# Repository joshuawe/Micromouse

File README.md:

# Micromouse
Micromouse TUM (Wintersemesester 2021/2022)

This is the repository of the Micromouse team of:
+ Marius
+ Michelle
+ Miriam
+ Joshua

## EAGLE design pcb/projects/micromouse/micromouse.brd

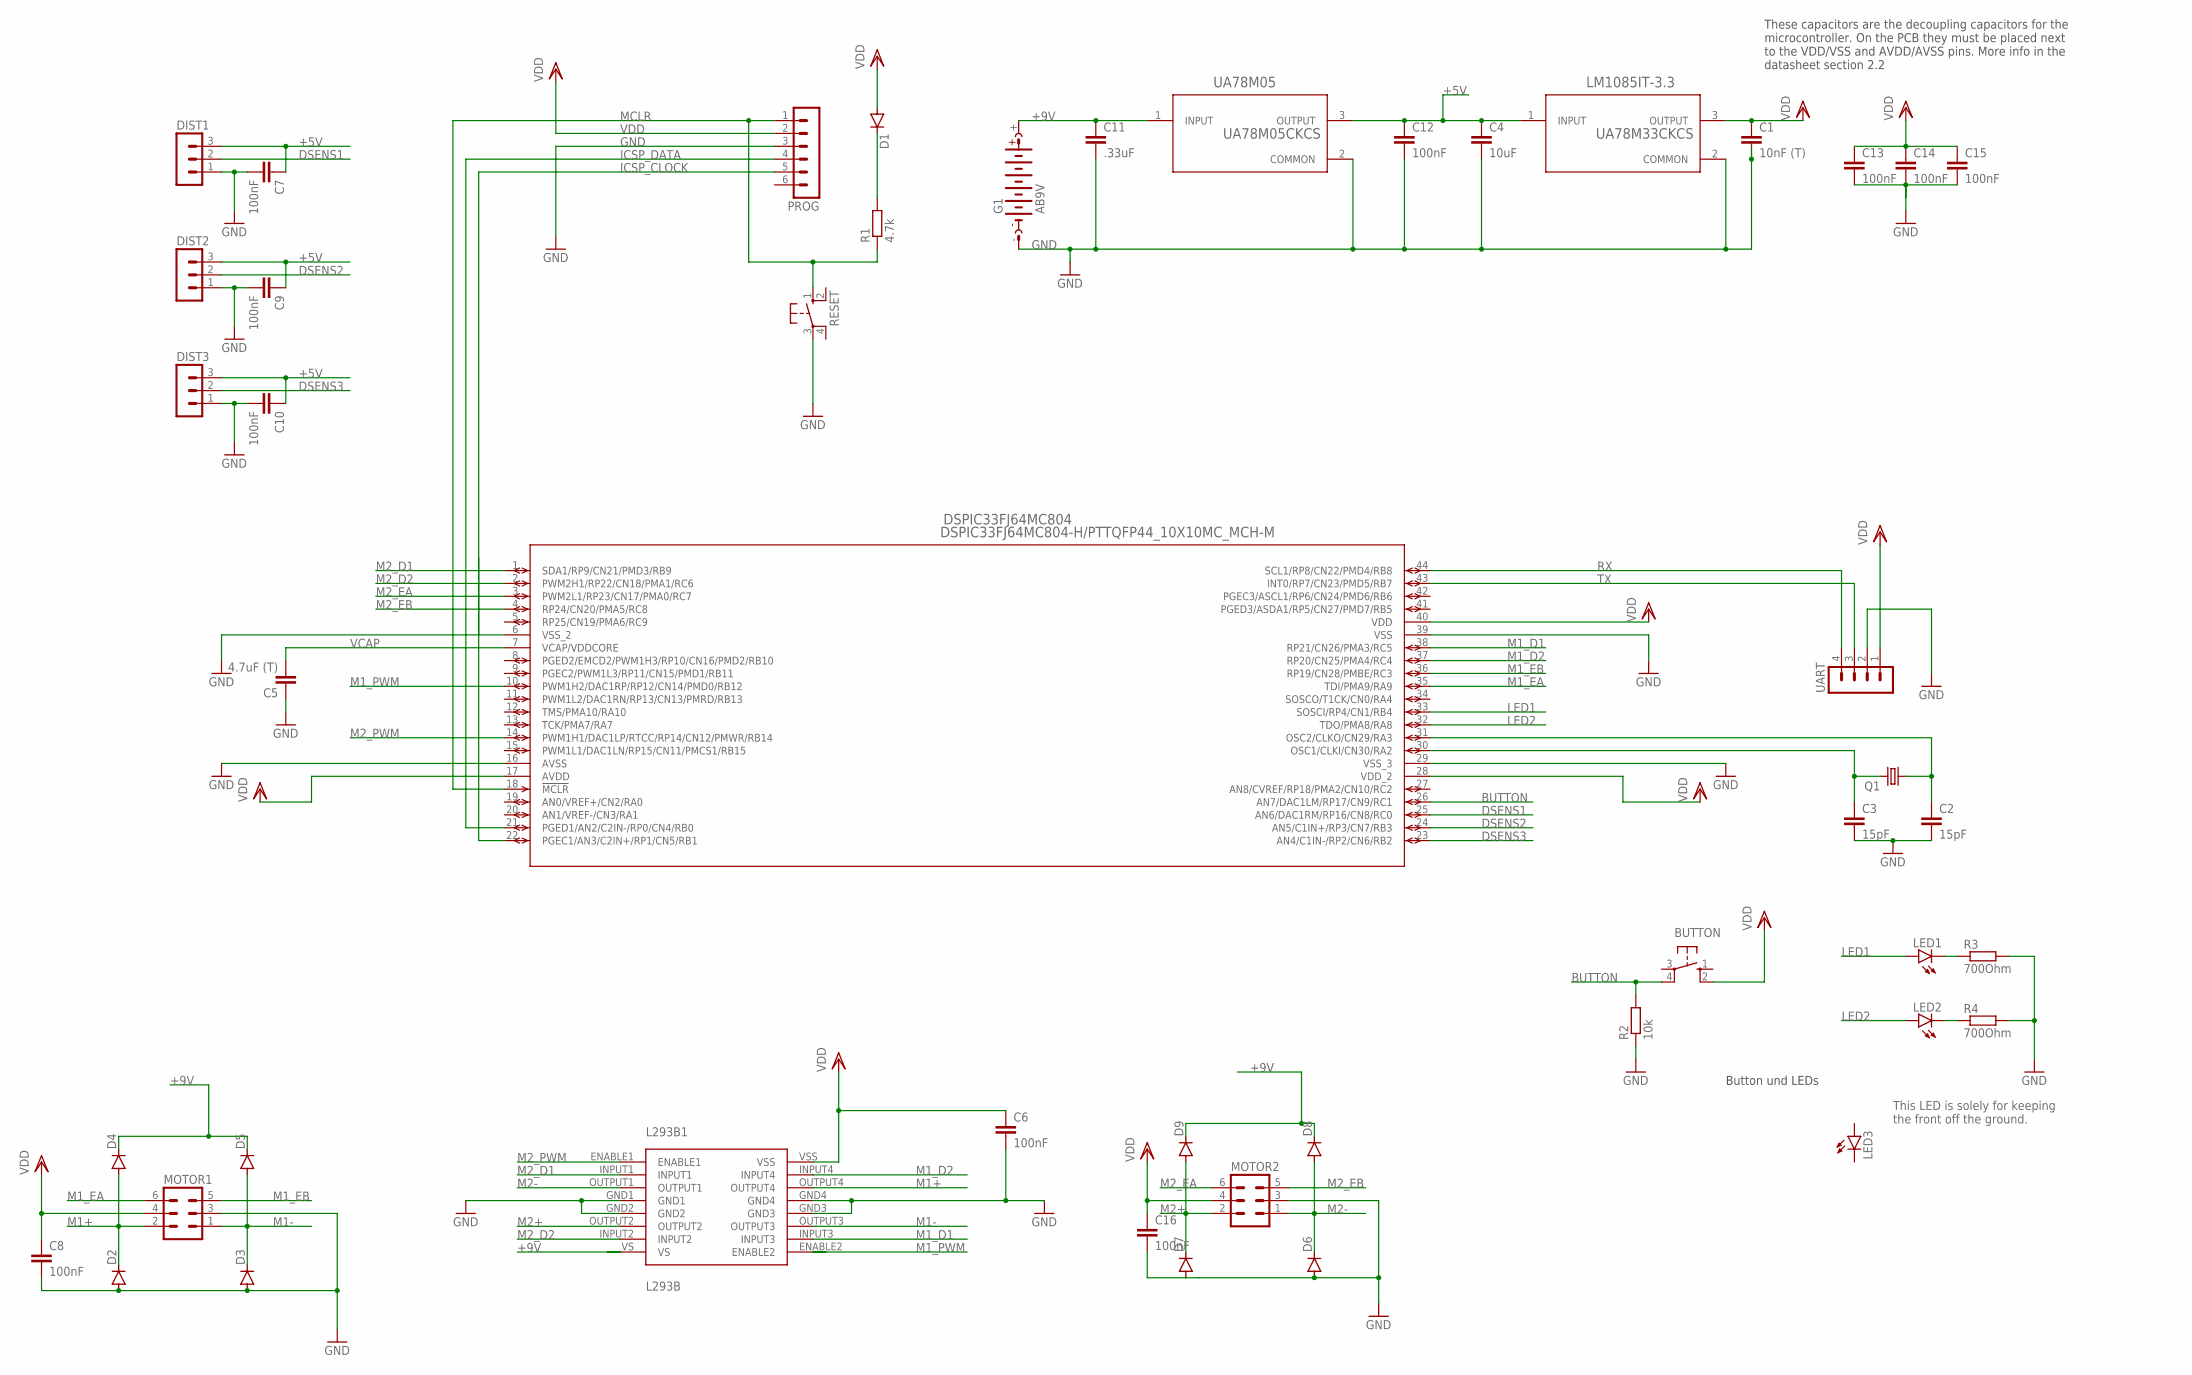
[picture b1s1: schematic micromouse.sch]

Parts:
BUTTON: 10-XX; B3F-10XX
C1: 10nF (T); C0805
C2, C3: 15pF; C0805
C4: 10uF; C0805
C5: 4.7uF (T); C0805
C6, C7, C8, C9, C10, C12, C13, C14, C15, C16: 100nF; C0805
C11: .33uF; C0805
D1, D2, D3, D4, D5, D6, D7, D8, D9: DIODE-SOD123; SOD123
DIST1, DIST2, DIST3: MA03-1
DSPIC33FJ64MC804: DSPIC33FJ64MC804-H/PTTQFP44_10X10MC_MCH-M; TQFP44_10X10MC_MCH-M
G1: AB9V
L293B1: L293B; L293P-DIP16
LED1, LED2: LEDCHIP-LED0805; CHIP-LED0805
LED3: LED5MM
LM1085IT-3.3: UA78M33CKCS; KCS0003B
MOTOR1, MOTOR2: MA03-2
PROG: MA06-1
Q1: CRYSTALHC49S; HC49/S
R1: 4.7k; R0805
R2: 10k; R0805
R3, R4: 700Ohm; R0805
RESET: 10-XX; B3F-10XX
UA78M05: UA78M05CKCS; KCS0003B
UART: MA04-1

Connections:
+5V: C4.1, C7.1, C9.1, C10.1, C12.1, DIST1.3, DIST2.3, DIST3.3, LM1085IT-3.3.1 (INPUT), UA78M05.3 (OUTPUT)
+9V: C11.1, D4.C, D5.C, D8.C, D9.C, G1.+, L293B1.VS, UA78M05.1 (INPUT)
BUTTON: BUTTON.4 (P1), DSPIC33FJ64MC804.26 (AN7/DAC1LM/RP17/CN9/RC1), R2.2
DSENS1: DIST1.2, DSPIC33FJ64MC804.25 (AN6/DAC1RM/RP16/CN8/RC0)
DSENS2: DIST2.2, DSPIC33FJ64MC804.24 (AN5/C1IN+/RP3/CN7/RB3)
DSENS3: DIST3.2, DSPIC33FJ64MC804.23 (AN4/C1IN-/RP2/CN6/RB2)
GND: C1.2, C2.2, C3.2, C4.2, C5.1, C6.2, C7.2, C8.2, C9.2, C10.2, C11.2, C12.2, C13.2, C14.2, C15.2, C16.2, D2.A, D3.A, D6.A, D7.A, DIST1.1, DIST2.1, DIST3.1, DSPIC33FJ64MC804.6 (VSS_2), DSPIC33FJ64MC804.16 (AVSS), DSPIC33FJ64MC804.29 (VSS_3), DSPIC33FJ64MC804.39 (VSS), G1.-, L293B1.GND1, L293B1.GND2, L293B1.GND3, L293B1.GND4, LM1085IT-3.3.2 (COMMON), MOTOR1.3, MOTOR2.3, PROG.3, R2.1, R3.2, R4.2, RESET.3, UA78M05.2 (COMMON), UART.2
ICSP_CLOCK: DSPIC33FJ64MC804.22 (PGEC1/AN3/C2IN+/RP1/CN5/RB1), PROG.5
ICSP_DATA: DSPIC33FJ64MC804.21 (PGED1/AN2/C2IN-/RP0/CN4/RB0), PROG.4
LED1: DSPIC33FJ64MC804.33 (SOSCI/RP4/CN1/RB4), LED1.A
LED2: DSPIC33FJ64MC804.32 (TDO/PMA8/RA8), LED2.A
M1+: D2.C, D4.A, L293B1.OUTPUT4, MOTOR1.2
M1-: D3.C, D5.A, L293B1.OUTPUT3, MOTOR1.1
M1_D1: DSPIC33FJ64MC804.38 (RP21/CN26/PMA3/RC5), L293B1.INPUT3
M1_D2: DSPIC33FJ64MC804.37 (RP20/CN25/PMA4/RC4), L293B1.INPUT4
M1_EA: DSPIC33FJ64MC804.35 (TDI/PMA9/RA9), MOTOR1.6
M1_EB: DSPIC33FJ64MC804.36 (RP19/CN28/PMBE/RC3), MOTOR1.5
M1_PWM: DSPIC33FJ64MC804.10 (PWM1H2/DAC1RP/RP12/CN14/PMD0/RB12), L293B1.ENABLE2
M2+: D7.C, D9.A, L293B1.OUTPUT2, MOTOR2.2
M2-: D6.C, D8.A, L293B1.OUTPUT1, MOTOR2.1
M2_D1: DSPIC33FJ64MC804.1 (SDA1/RP9/CN21/PMD3/RB9), L293B1.INPUT1
M2_D2: DSPIC33FJ64MC804.2 (PWM2H1/RP22/CN18/PMA1/RC6), L293B1.INPUT2
M2_EA: DSPIC33FJ64MC804.3 (PWM2L1/RP23/CN17/PMA0/RC7), MOTOR2.6
M2_EB: DSPIC33FJ64MC804.4 (RP24/CN20/PMA5/RC8), MOTOR2.5
M2_PWM: DSPIC33FJ64MC804.14 (PWM1H1/DAC1LP/RTCC/RP14/CN12/PMWR/RB14), L293B1.ENABLE1
MCLR: DSPIC33FJ64MC804.18 (!MCLR), PROG.1, R1.1, RESET.1 (S)
unnamed: C3.1, DSPIC33FJ64MC804.30 (OSC1/CLKI/CN30/RA2), Q1.2
unnamed: C2.1, DSPIC33FJ64MC804.31 (OSC2/CLKO/CN29/RA3), Q1.1
unnamed: D1.C, R1.2
unnamed: LED1.C, R3.1
unnamed: LED2.C, R4.1
RX: DSPIC33FJ64MC804.44 (SCL1/RP8/CN22/PMD4/RB8), UART.4
TX: DSPIC33FJ64MC804.43 (INT0/RP7/CN23/PMD5/RB7), UART.3
VCAP: C5.2, DSPIC33FJ64MC804.7 (VCAP/VDDCORE)
VDD: BUTTON.2 (S1), C1.1, C6.1, C8.1, C13.1, C14.1, C15.1, C16.1, D1.A, DSPIC33FJ64MC804.17 (AVDD), DSPIC33FJ64MC804.28 (VDD_2), DSPIC33FJ64MC804.40 (VDD), L293B1.VSS, LM1085IT-3.3.3 (OUTPUT), MOTOR1.4, MOTOR2.4, PROG.2, UART.1

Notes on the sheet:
These capacitors are the decoupling capacitors for the microcontroller. On the PCB they must be placed next to the VDD/VSS and AVDD/AVSS pins. More info in the datasheet section 2.2
Button und LEDs
This LED is solely for keeping the front off the ground.

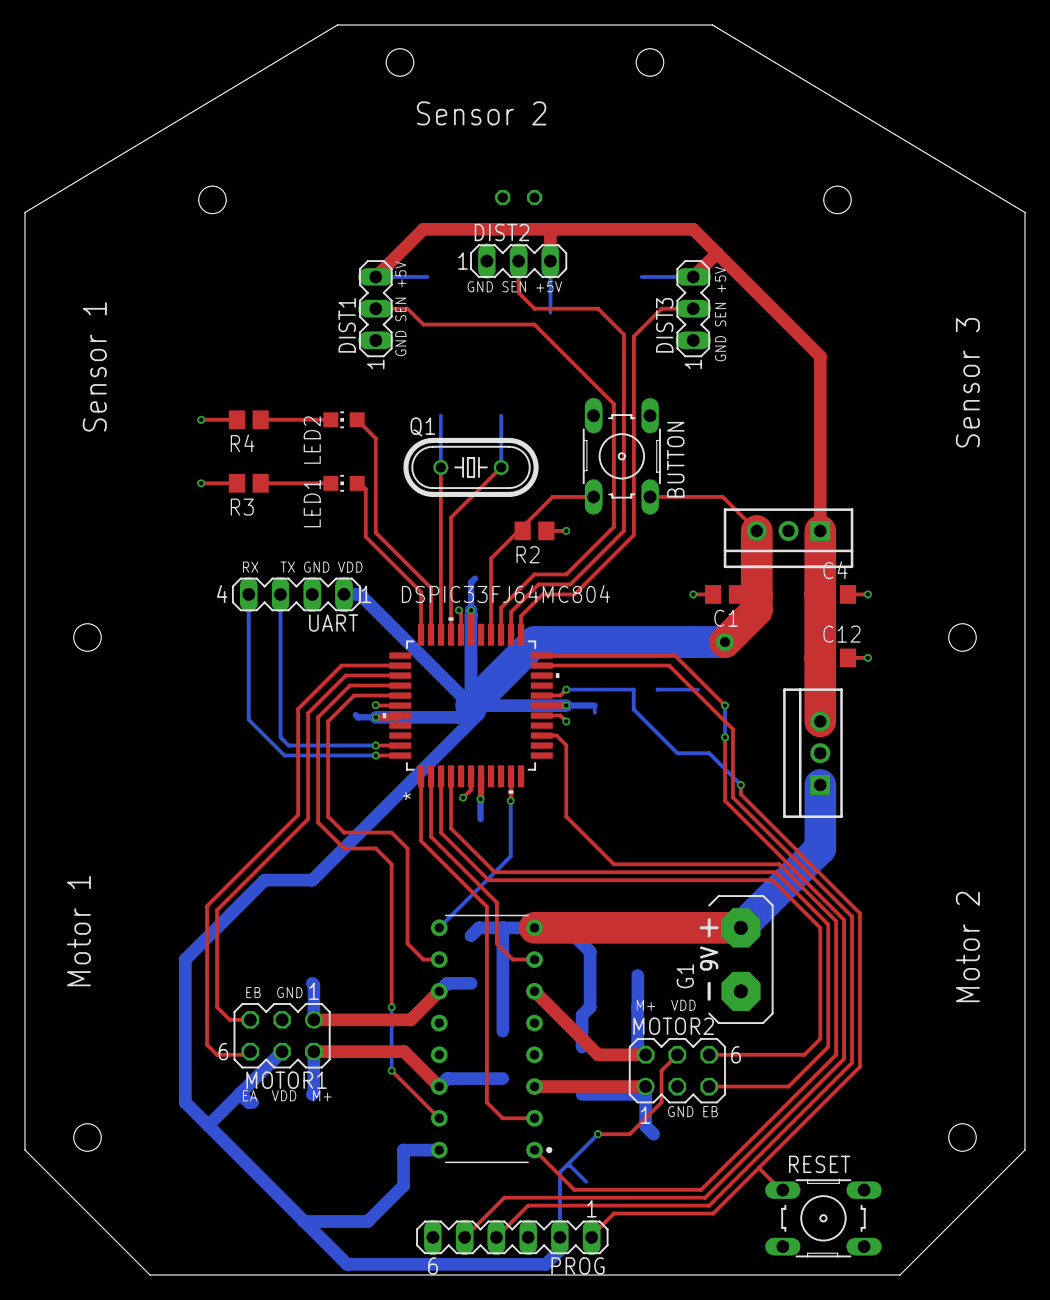
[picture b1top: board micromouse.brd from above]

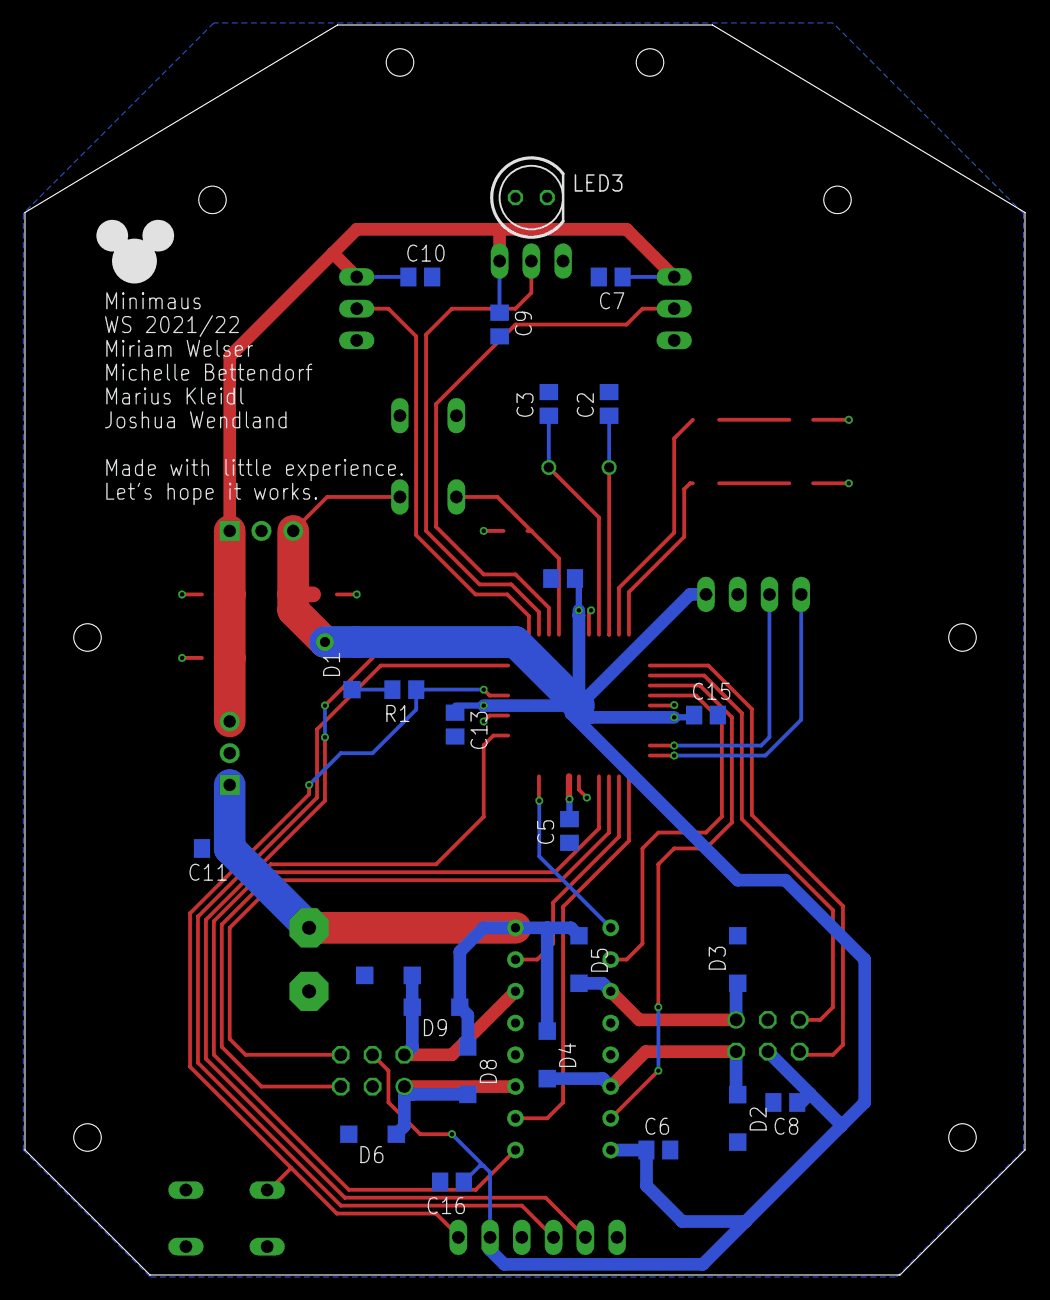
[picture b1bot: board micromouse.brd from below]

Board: 2 copper layers, 80.0 x 100.0 mm, 47 parts (24 on the bottom side), 35 nets.

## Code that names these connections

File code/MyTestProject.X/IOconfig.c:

#include "xc.h"
#include "IOconfig.h"
#include "myPWM.h"



//*** sets up the pins in a certain configuration
void setupIO()
{

    int i;
    //AD1PCFGL=0xFFFF; //all pins are now digital, by default they are analogue
    AD1PCFGL = 0b1111111110001111; // -> pin 4, 5, and 6 are analog pins
                        // AN0 and AN5 are the only inputs !!!CHANGE HERE!!!
                        // AD1 Part Configuration -> by default all bits are 0
                        // Circuit Diagramm: IO6 connects to RB3
                        // Data Sheet RB3 is AN5 (fixed location on the chip)
                        // by default analog functionality
                        // AD Converter does not work


    // LED configuration (set them as output)
    // LED1 is pin 33 (RB4)
    TRISBbits.TRISB4 = 0;
    // LED2 is pin 32 (RA8)
    TRISAbits.TRISA8 = 0;

    // Button configuration (set them as input)
    // BUTTON is pin 26 (RC1)
    TRISCbits.TRISC1 = 1;

    //PIN MAPPING
    // ***** which PIN talks to which PIN ? *****
    // ***** define the multiplexers ! *****

    //before we map, we need to unlock
    __builtin_write_OSCCONL(OSCCON & 0xbf); // clear bit 6 (unlock, they are usually write protected)

    // UART configuration:
    //              RX = PIN43/RB7/RP7
    //              TX = PIN44/RB8/RP8
    // PERIPHERAL receives data from which INPUT
    // Map U1 RX to RP7
    RPINR18bits.U1RXR = 7;
    // OUTPUT PIN receives data from which PERIPHERAL,
    // see table 11-2 in datasheet to check peripheral codes
    // Map RP8 to U1 TX (other way than mapping RX)
    RPOR4bits.RP8R = 0b00011;
    TRISBbits.TRISB8=0;// UART1 TX

    // Encoder configuration
    // Motor 1
    // Pin 42 (RP6) Channel A
    // Pin 36 (RP19) Channel B
    TRISAbits.TRISA9 = 1; // Through error, RA9 is also connected to the encoder, so we need it as an input.
    TRISBbits.TRISB6 = 1;
    TRISCbits.TRISC3 = 1;
    RPINR14bits.QEA1R = 6;
    RPINR14bits.QEB1R = 19;
    
    // Motor 2
    // Pin 3 (RP23) Channel A
    // Pin 4 (RP24) Channel B
    TRISCbits.TRISC7 = 1;
    TRISCbits.TRISC8 = 1;
    RPINR16bits.QEA2R = 23;
    RPINR16bits.QEB2R = 24;

    // Motor 1 configuration (left motor)
    TRISCbits.TRISC5 = 0;  // Direction 1, pin 38, RC5
    TRISCbits.TRISC4 = 0;  // Direction 2, pin 37, RC4
    TRISBbits.TRISB12 = 0; // PWM 1, pin 10, PWM1H2, RB12
    LATCbits.LATC5 = 0;  // Pin 38
    LATCbits.LATC4 = 0;  // Pin 37
    LATBbits.LATB12 = 0; // Pin 10
    
    // Motor 2 configuration (right motor)
    TRISBbits.TRISB9 = 0;  // Direction 1, pin 1, RB9
    TRISCbits.TRISC6 = 0;  // Direction 2, pin 2, RC6
    TRISBbits.TRISB14 = 0; // PWM 2, pin 14, PWM1H1, RB14
    LATBbits.LATB9 = 0;  // Pin 1
    LATCbits.LATC6 = 0;  // Pin 2
    LATBbits.LATB14 = 0; // Pin 14

    //after mapping we lock again
     __builtin_write_OSCCONL(OSCCON | 0x40); // Lock PPS registers (lock again!)

    for (i = 0; i < 30000; i++); // short dirty delay for changes to take effect,

}

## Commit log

2022-01-11 bestellungen unfertig
2022-01-12 Updated the Bestellliste
2022-01-12 updated BEstellliste
2022-01-14 with comments from meeting with Alex
2022-01-18 Add PCB
2022-01-18 Add value for resistors for LEDs
2022-01-20 Add solder pad for distance sensor and battery
2022-01-21 Use TO-220 for voltage reguators
2022-01-21 Recreate board layout
2022-01-21 Position components
2022-01-21 Most wiring done
2022-01-21 Complete wiring
2022-01-21 Ground plane and ground connections
2022-01-21 Not sure what these library changes are
2022-01-25 Some code
2022-01-25 code structure
2022-01-25 Bestellliste aktualisiert + MotorControl.c
2022-01-25 Replace LED with 0805 package
2022-01-25 Make motor and encoder work
2022-01-25 Import design rules
2022-01-25 Remove restricted areas for microship
2022-01-25 Fix overlapping errors
2022-01-25 mapping added
2022-01-29 Import new board shape
2022-01-30 Replace some pin connectors
2022-01-31 Routing for new PCB
2022-02-01 Update reset button
2022-02-07 LED and resistor value
2022-02-07 Required parts
2022-02-08 Bestellliste aktualisiert
2022-02-09 neuer Widerstand
2022-02-10 Final PCB touches
2022-02-11 code structure + bestellliste updated
2022-02-16 Update Bestellliste
    - Widerstände
    - Diode
    - Sensoren
    - Räder
2022-02-17 Updated voltage regulator and crystal
2022-03-15 Updated received parts
2022-03-16 Remove files from Git index that are different for every user
2022-03-16 Resolve conflict in config file
2022-03-16 fixup! Remove files from Git index that are different for every user
2022-03-16 Correct device
2022-03-16 bugs fixed
2022-03-17 map improved
2022-03-18 Setup 16MHz oscillator
2022-03-18 Fix compile errors in mapping.c
2022-03-18 Enable LEDs
2022-03-18 Active timer
2022-03-18 Remove some trailing whitespace
2022-03-18 Activate button
2022-03-18 fixup! Active timer
2022-03-18 fixup! fixup! Active timer
2022-03-18 Clear up UART configuration
2022-03-18 Bestelliste mit Farbencodierung
2022-03-18 Setup code for motor PWM
2022-03-20 explore mode added
2022-03-21 UART working now with Baudrate 9600
2022-03-21 Fix pins for UART
2022-03-21 Proximity sensors define motor speed
2022-03-22 mapping bug fixed
2022-03-23 Make one encoder work
2022-03-24 Make second encoder work
2022-03-24 Read values from distance sensors /proximity sensors
2022-03-24 sensor calibrations
2022-03-24 motor speed function easy
2022-03-24 path planning added + pictures
2022-03-24 bug fixed
2022-03-24 Print proximity sensor values
2022-03-24 Fix garbage at the begining of bluetooth transmission
2022-03-24 Clean up logging
2022-03-24 method descriptions added
2022-03-28 bluetooth connection, introduced config file
2022-03-28 added usage of profiles
2022-03-28 added pyarsing
2022-03-28 functions for communication with protocol
2022-03-28 proper parsing and passing of variables
2022-03-28 dash app first version
2022-03-29 new files controller.c and .h
    ✨controller.c and .h
2022-03-29 using global variable (unrelieable)
2022-03-29 🎨 change of struct declarations
    🎨 change of struct declarations
2022-03-29 🎨 edit MotorControl
2022-03-30 Some compiler fixes in MotorControl.h
2022-03-30 Add UART parser
2022-03-31 serial Studio
2022-03-31 Dash App
2022-03-31 ftoa now returns a pointer to char array
2022-03-31 Config file for Serial Studio
2022-03-31 updated interrupts
2022-03-31 included ltoa(_) and updated header files
2022-03-31 ups vergessene, sachen kommen hier
2022-03-31 Make encoder work correctly
2022-03-31 ✨ added PID controller (not finished)
    ✨ header motor control and functions in *.c updated
2022-04-01 added global variables + added updateSpeed functin
2022-04-01 updated the new encoder function
2022-04-01 added deltaT variable for loop frequency
2022-04-01 void updateWheelDistanceRotation(void)
2022-04-01 updated function updateWheelDistanceRotation(_)
2022-04-02 mapping and ICC finished
2022-04-02 ✨ almost finished PID controller and changed WHEEL RADIUS in encoder.c
2022-04-02 ✨ added calculation of turning speed in rounds / s
2022-04-02 🎨 changed names of new variables
2022-04-02 🎨 edit of controller and minor changes in other files
    - definition of constants
    - change of error for velocity control
    - optional feedforward term
    - comments and descriptions of functions
    - init control cycle
    - update header
2022-04-02 ✨ stops when a wall is in front to avoid collision
2022-04-03 logic error fixed
2022-04-03 path planning fixed
2022-04-03 path planning updated
2022-04-03 ✨ calibration implemented and output for debugging
2022-04-03 picture path planning added
2022-04-04 Updated Mouse measurements for currrent (old) CAD version, which we will use until the new 3D printed parts arrive
2022-04-04 Change arguments to pointers, so values get stored
2022-04-04 Rework controller and measurements
2022-04-04 updated speed calculation and more
2022-04-04 Fixed speed calculation issues
2022-04-05 new controller values
2022-04-05 Updated config file, now includes speeds
2022-04-05 Enable command over Bluetooth
2022-04-05 Remove unused print functions
2022-04-05 Edited function description
2022-04-05 Fixed logic in function checkOutputIfItExceedsMaximum
2022-04-05 With velocity control depending on distance
2022-04-05 added Distance to goal
2022-04-06 Work of the day, controller working, wall following working
2022-04-06 icc changed
2022-04-06 Refactor error from proximity sensors
2022-04-06 make movements work!!
2022-04-06 minor cleanup
2022-04-06 make exploring mode work
2022-04-06 contains next Goal info
2022-04-06 improve contoller
2022-04-06 mapping improvements
2022-04-06 add debugging for mapping
2022-04-06 approach speed to goal is quadratic
2022-04-06 updated description
2022-04-06 better Controller, adjusted cell size, added front calibration
2022-04-06 patched
2022-04-06 corrected P_D differential value
2022-04-07 Logic to first drive to the start
2022-04-07 exploring improved
2022-04-13 path planning improved
2022-04-13 Add comment about problem
2022-04-25 Corrected prox sensor plot
2022-04-27 figure speed goal
2022-04-27 updated graph
2022-04-27 "linear" -> "cubic"
2022-04-27 smaller shift of cubic line
2022-04-27 added d_tolerance
2022-04-29 included quantization
2022-04-29 adjusted binary search for Motor PWM
2022-04-29 Add 3x3 video
2022-04-29 6x6 video

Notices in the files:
parts and their libraries:
COPYRIGHT: Copyright (C) 2022 Ultra Librarian. All rights reserved.
